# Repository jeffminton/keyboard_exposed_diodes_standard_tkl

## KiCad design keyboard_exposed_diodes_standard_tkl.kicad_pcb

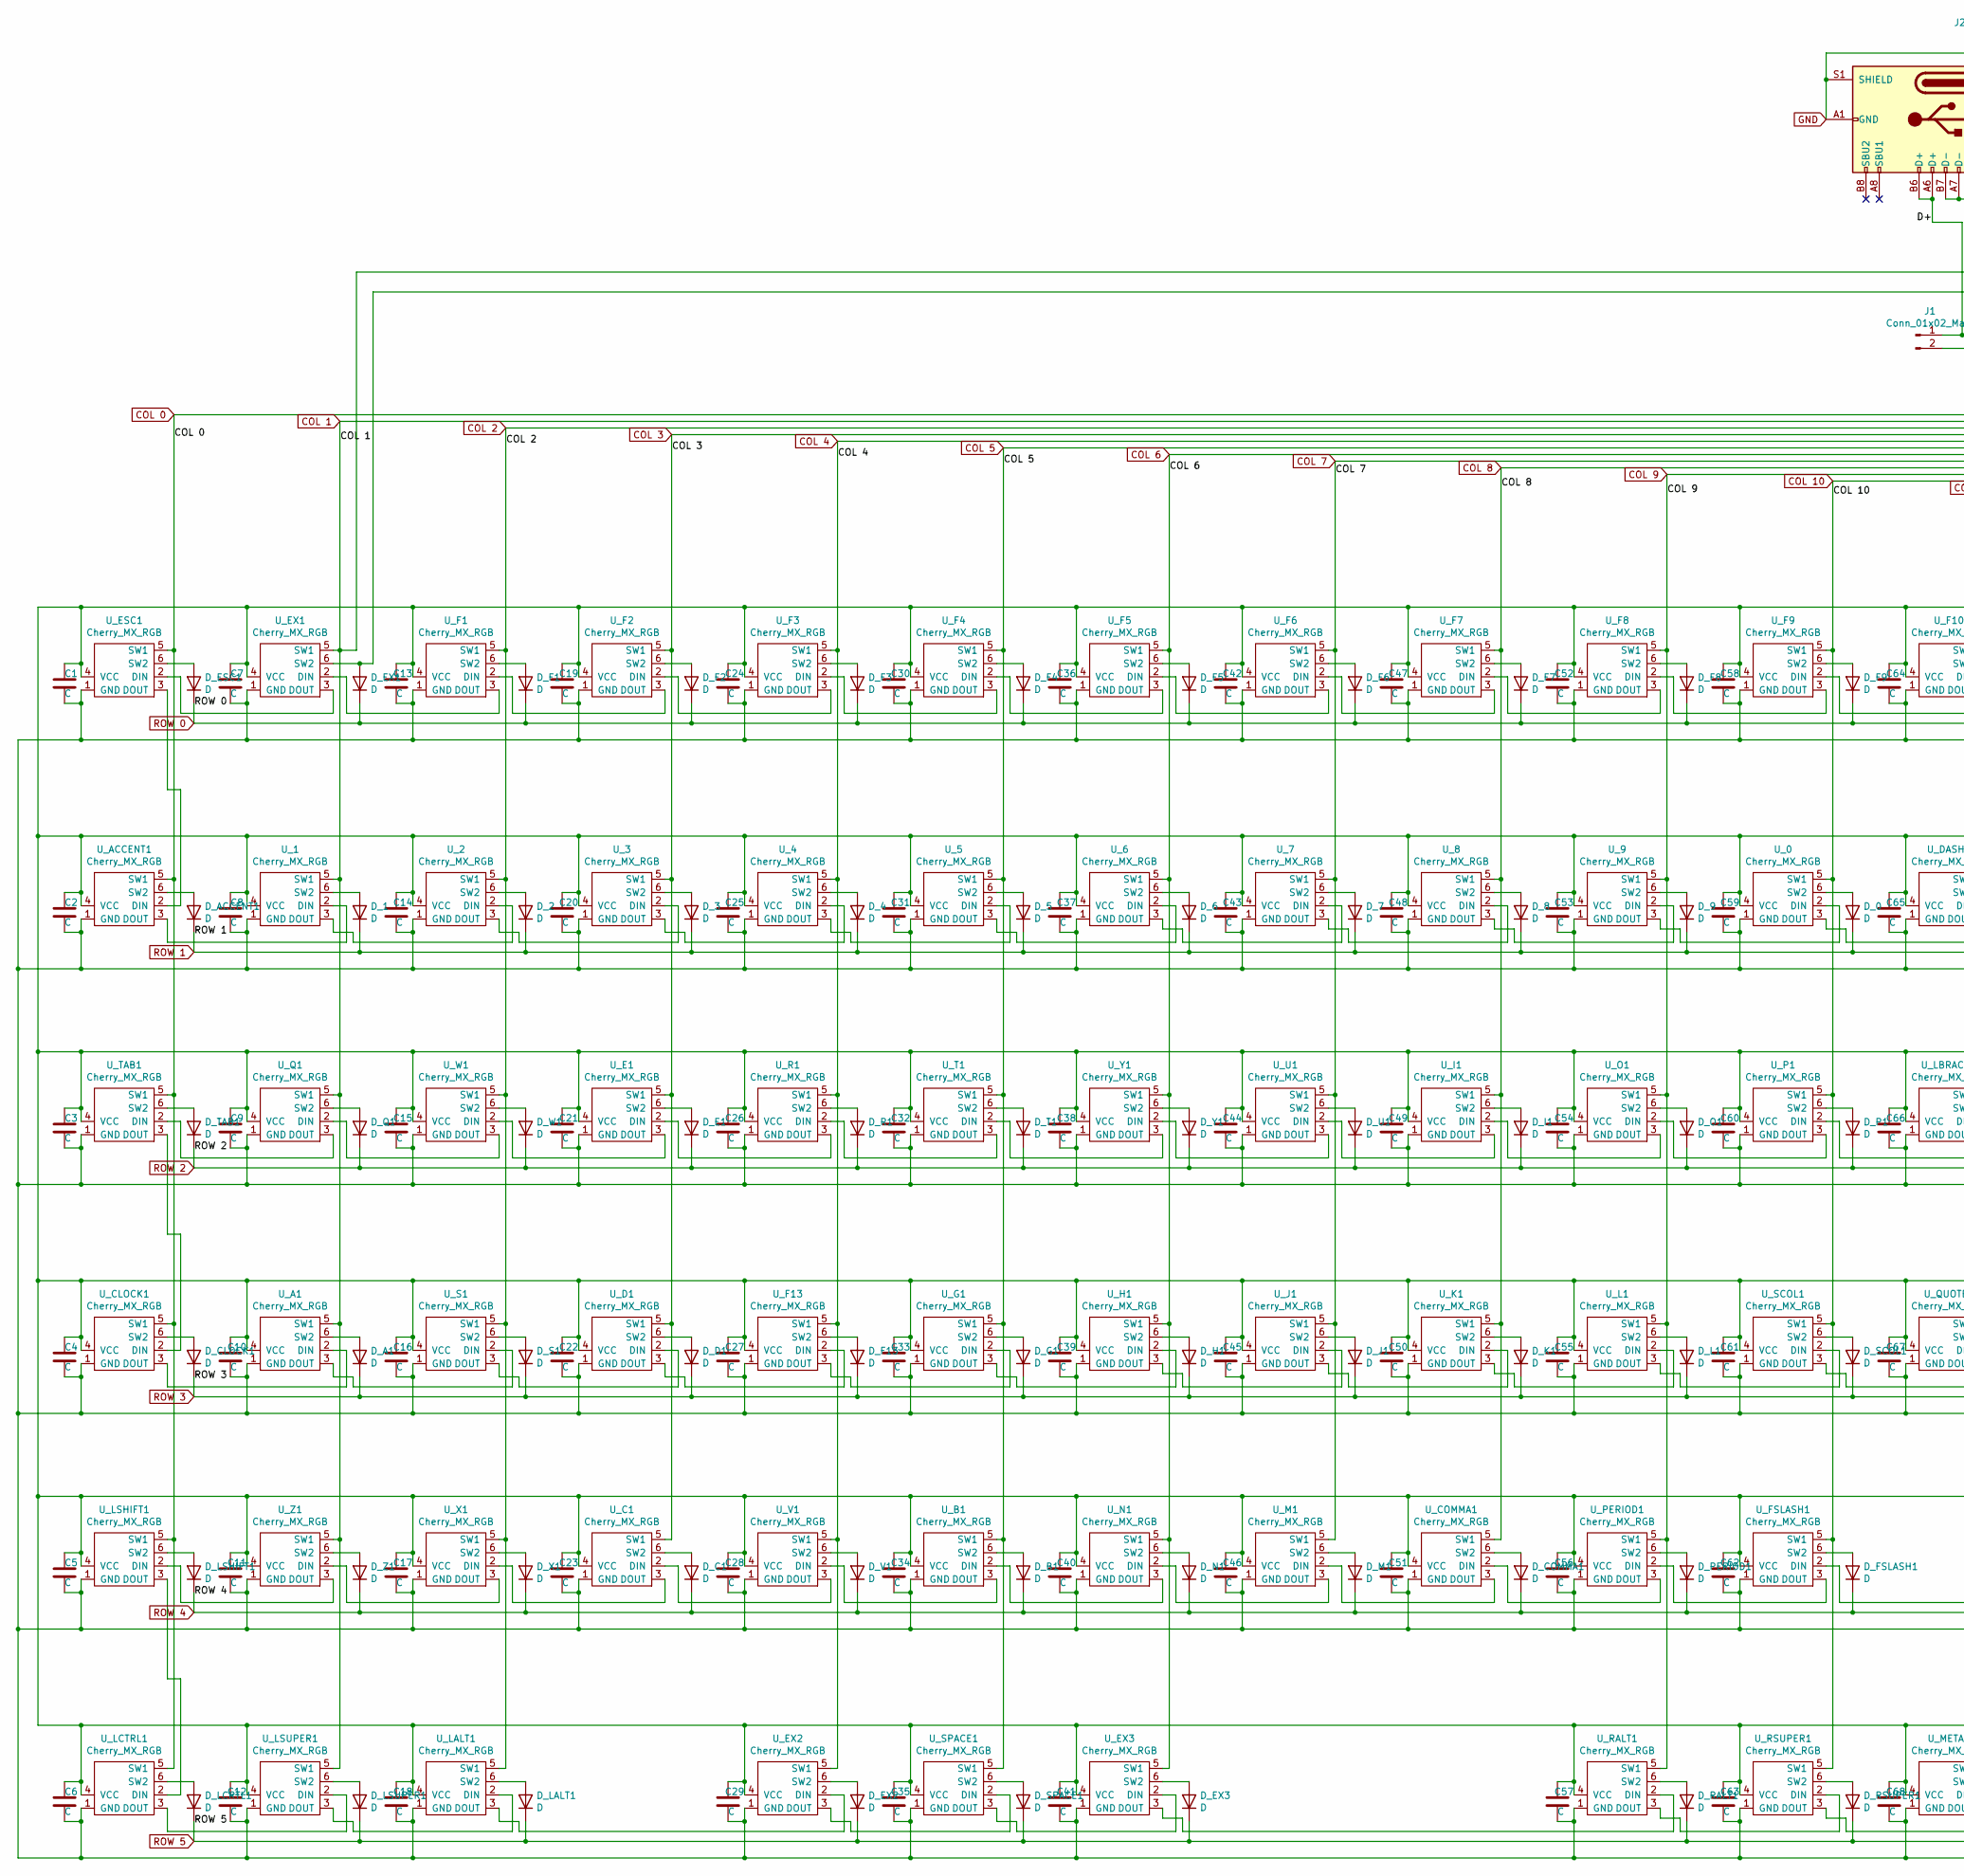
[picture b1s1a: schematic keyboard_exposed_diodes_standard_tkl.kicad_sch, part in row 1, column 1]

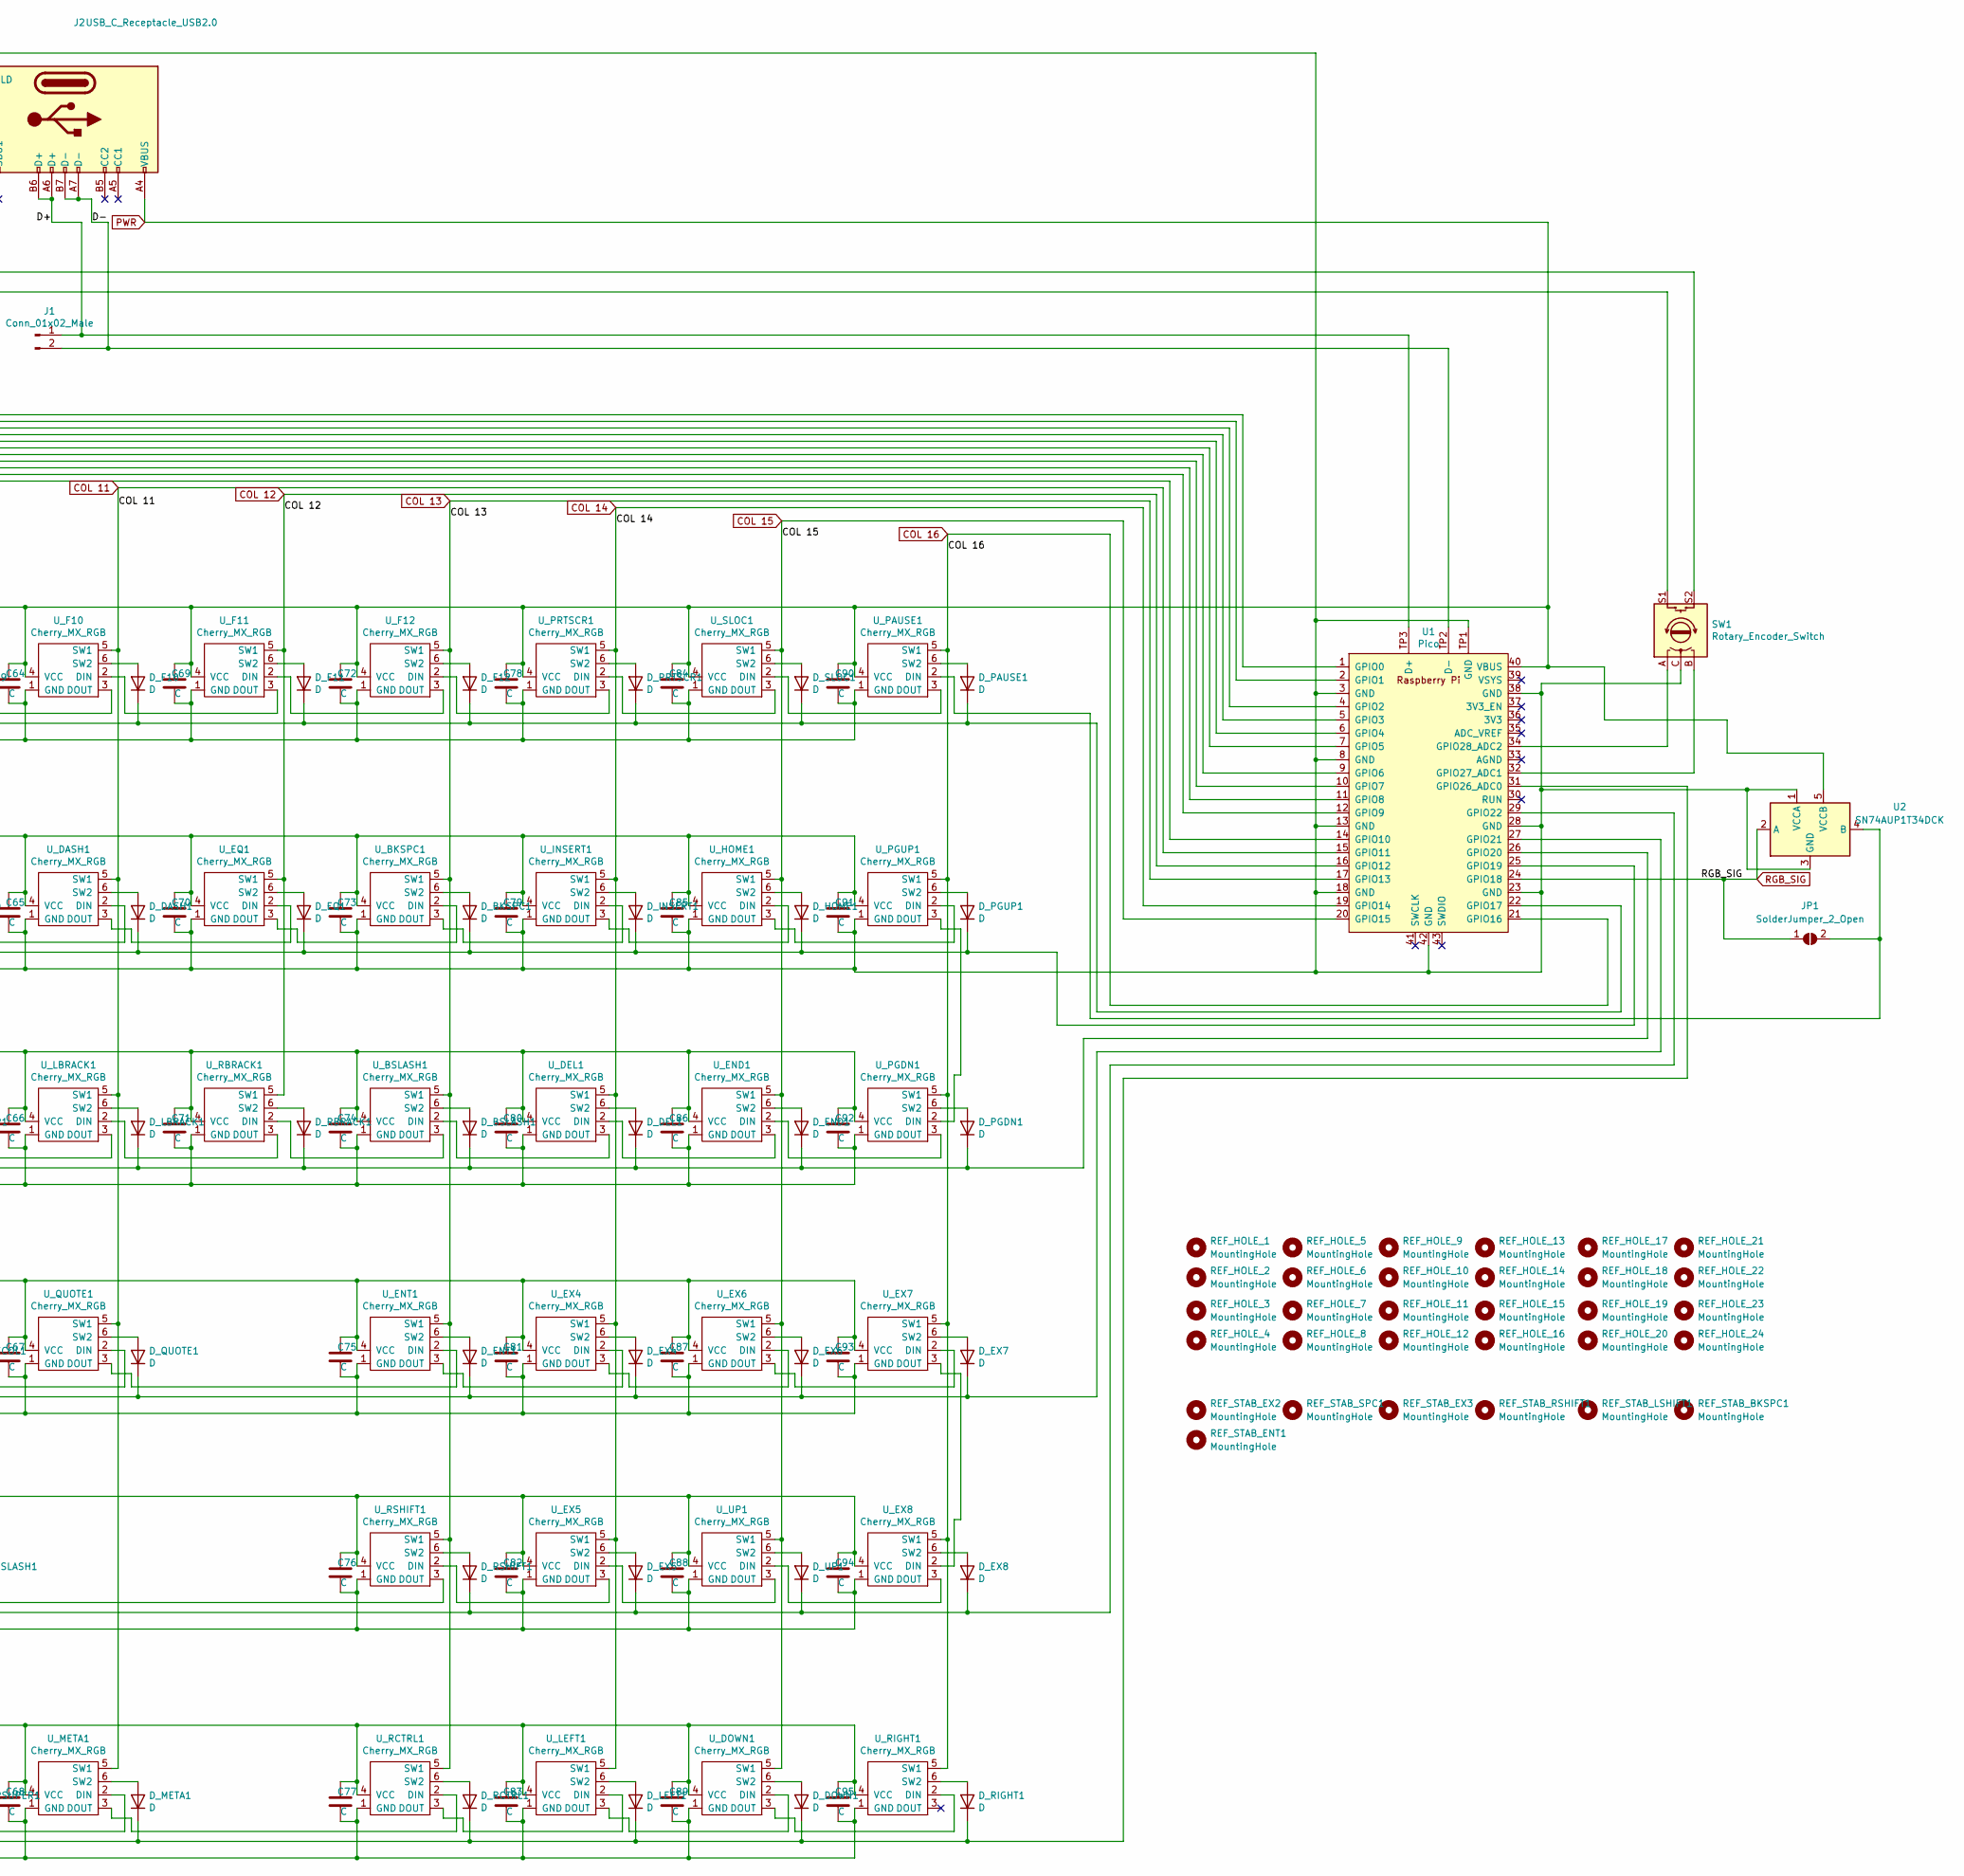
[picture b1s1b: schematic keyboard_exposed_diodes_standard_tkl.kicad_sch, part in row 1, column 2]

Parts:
C1, C2, C3, C4, C5, C6, C7, C8, C9, C10, C11, C12, C13, C14, C15, C16, C17, C18, C19, C20, C21, C22, C23, C24, C25, C26, C27, C28, C29, C30, C31, C32, C33, C34, C35, C36, C37, C38, C39, C40, C41, C42, C43, C44, C45, C46, C47, C48, C49, C50, C51, C52, C53, C54, C55, C56, C57, C58, C59, C60, C61, C62, C63, C64, C65, C66, C67, C68, C69, C70, C71, C72, C73, C74, C75, C76, C77, C78, C79, C80, C81, C82, C83, C84, C85, C86, C87, C88, C89, C90, C91, C92, C93, C94, C95: C; C_0805_2012Metric
D_0, D_1, D_2, D_3, D_4, D_5, D_6, D_7, D_8, D_9: D; D_DO-35_SOD27_P7.62mm_Horizontal
D_A1: D; D_DO-35_SOD27_P7.62mm_Horizontal
D_ACCENT1: D; D_DO-35_SOD27_P7.62mm_Horizontal
D_B1: D; D_DO-35_SOD27_P7.62mm_Horizontal
D_BKSPC1: D; D_DO-35_SOD27_P7.62mm_Horizontal
D_BSLASH1: D; D_DO-35_SOD27_P7.62mm_Horizontal
D_C1: D; D_DO-35_SOD27_P7.62mm_Horizontal
D_CLOCK1: D; D_DO-35_SOD27_P7.62mm_Horizontal
D_COMMA1: D; D_DO-35_SOD27_P7.62mm_Horizontal
D_D1: D; D_DO-35_SOD27_P7.62mm_Horizontal
D_DASH1: D; D_DO-35_SOD27_P7.62mm_Horizontal
D_DEL1: D; D_DO-35_SOD27_P7.62mm_Horizontal
D_DOWN1: D; D_DO-35_SOD27_P7.62mm_Horizontal
D_E1: D; D_DO-35_SOD27_P7.62mm_Horizontal
D_END1: D; D_DO-35_SOD27_P7.62mm_Horizontal
D_ENT1: D; D_DO-35_SOD27_P7.62mm_Horizontal
D_EQ1: D; D_DO-35_SOD27_P7.62mm_Horizontal
D_ESC1: D; D_DO-35_SOD27_P7.62mm_Horizontal
D_EX1, D_EX2, D_EX3, D_EX4, D_EX5, D_EX6, D_EX7, D_EX8: D; D_DO-35_SOD27_P7.62mm_Horizontal
D_F1, D_F2, D_F3, D_F4, D_F5, D_F6, D_F7, D_F8, D_F9, D_F10, D_F11, D_F12, D_F13: D; D_DO-35_SOD27_P7.62mm_Horizontal
D_FSLASH1: D; D_DO-35_SOD27_P7.62mm_Horizontal
D_G1: D; D_DO-35_SOD27_P7.62mm_Horizontal
D_H1: D; D_DO-35_SOD27_P7.62mm_Horizontal
D_HOME1: D; D_DO-35_SOD27_P7.62mm_Horizontal
D_I1: D; D_DO-35_SOD27_P7.62mm_Horizontal
D_INSERT1: D; D_DO-35_SOD27_P7.62mm_Horizontal
D_J1: D; D_DO-35_SOD27_P7.62mm_Horizontal
D_K1: D; D_DO-35_SOD27_P7.62mm_Horizontal
D_L1: D; D_DO-35_SOD27_P7.62mm_Horizontal
D_LALT1: D; D_DO-35_SOD27_P7.62mm_Horizontal
D_LBRACK1: D; D_DO-35_SOD27_P7.62mm_Horizontal
D_LCRTL1: D; D_DO-35_SOD27_P7.62mm_Horizontal
D_LEFT1: D; D_DO-35_SOD27_P7.62mm_Horizontal
D_LSHIFT1: D; D_DO-35_SOD27_P7.62mm_Horizontal
D_LSUPER1: D; D_DO-35_SOD27_P7.62mm_Horizontal
D_M1: D; D_DO-35_SOD27_P7.62mm_Horizontal
D_META1: D; D_DO-35_SOD27_P7.62mm_Horizontal
D_N1: D; D_DO-35_SOD27_P7.62mm_Horizontal
D_O1: D; D_DO-35_SOD27_P7.62mm_Horizontal
D_P1: D; D_DO-35_SOD27_P7.62mm_Horizontal
D_PAUSE1: D; D_DO-35_SOD27_P7.62mm_Horizontal
D_PERIOD1: D; D_DO-35_SOD27_P7.62mm_Horizontal
D_PGDN1: D; D_DO-35_SOD27_P7.62mm_Horizontal
D_PGUP1: D; D_DO-35_SOD27_P7.62mm_Horizontal
D_PRTSCR1: D; D_DO-35_SOD27_P7.62mm_Horizontal
D_Q1: D; D_DO-35_SOD27_P7.62mm_Horizontal
D_QUOTE1: D; D_DO-35_SOD27_P7.62mm_Horizontal
D_R1: D; D_DO-35_SOD27_P7.62mm_Horizontal
D_RALT1: D; D_DO-35_SOD27_P7.62mm_Horizontal
D_RBRACK1: D; D_DO-35_SOD27_P7.62mm_Horizontal
D_RCTRL1: D; D_DO-35_SOD27_P7.62mm_Horizontal
D_RIGHT1: D; D_DO-35_SOD27_P7.62mm_Horizontal
D_RSHIFT1: D; D_DO-35_SOD27_P7.62mm_Horizontal
D_RSUPER1: D; D_DO-35_SOD27_P7.62mm_Horizontal
D_S1: D; D_DO-35_SOD27_P7.62mm_Horizontal
D_SCOL1: D; D_DO-35_SOD27_P7.62mm_Horizontal
D_SLOC1: D; D_DO-35_SOD27_P7.62mm_Horizontal
D_SPACE1: D; D_DO-35_SOD27_P7.62mm_Horizontal
D_T1: D; D_DO-35_SOD27_P7.62mm_Horizontal
D_TAB1: D; D_DO-35_SOD27_P7.62mm_Horizontal
D_U1: D; D_DO-35_SOD27_P7.62mm_Horizontal
D_UP1: D; D_DO-35_SOD27_P7.62mm_Horizontal
D_V1: D; D_DO-35_SOD27_P7.62mm_Horizontal
D_W1: D; D_DO-35_SOD27_P7.62mm_Horizontal
D_X1: D; D_DO-35_SOD27_P7.62mm_Horizontal
D_Y1: D; D_DO-35_SOD27_P7.62mm_Horizontal
D_Z1: D; D_DO-35_SOD27_P7.62mm_Horizontal
J1: Conn_01x02_Male; PinHeader_1x02_P2.54mm_Vertical
J2: USB_C_Receptacle_USB2.0; USB_C_Receptacle_GCT_USB4085
JP1: SolderJumper_2_Open; SolderJumper-2_P1.3mm_Open_RoundedPad1.0x1.5mm
REF_HOLE_1, REF_HOLE_2, REF_HOLE_3, REF_HOLE_4, REF_HOLE_5, REF_HOLE_6, REF_HOLE_7, REF_HOLE_8, REF_HOLE_9, REF_HOLE_10, REF_HOLE_11, REF_HOLE_12, REF_HOLE_13, REF_HOLE_14, REF_HOLE_15, REF_HOLE_16, REF_HOLE_17, REF_HOLE_18, REF_HOLE_19, REF_HOLE_20, REF_HOLE_21, REF_HOLE_22, REF_HOLE_23, REF_HOLE_24: MountingHole; MountingHole_4.3mm_M4
REF_STAB_BKSPC1: MountingHole; Stabilizer_Cherry_MX_2u
REF_STAB_ENT1: MountingHole; Stabilizer_Cherry_MX_2u
REF_STAB_EX2, REF_STAB_EX3: MountingHole; Stabilizer_Cherry_MX_2u
REF_STAB_LSHIFT1: MountingHole; Stabilizer_Cherry_MX_2u
REF_STAB_RSHIFT1: MountingHole; Stabilizer_Cherry_MX_2u
REF_STAB_SPC1: MountingHole; Stabilizer_Cherry_MX_2u
SW1: Rotary_Encoder_Switch; Rotary_Encoder_Switched_PEC11R
U1: Pico; RPi_Pico_SMD_TH
U2: SN74AUP1T34DCK; SOT-353_SC-70-5
U_0, U_1, U_2, U_3, U_4, U_5, U_6, U_7, U_8, U_9: Cherry_MX_RGB; Cherry-MX_PCB-Mounted_LTST-A683CEGBW_Mill-Max-7305
U_A1: Cherry_MX_RGB; Cherry-MX_PCB-Mounted_LTST-A683CEGBW_Mill-Max-7305
U_ACCENT1: Cherry_MX_RGB; Cherry-MX_PCB-Mounted_LTST-A683CEGBW_Mill-Max-7305
U_B1: Cherry_MX_RGB; Cherry-MX_PCB-Mounted_LTST-A683CEGBW_Mill-Max-7305
U_BKSPC1: Cherry_MX_RGB; Cherry-MX_PCB-Mounted_LTST-A683CEGBW_Mill-Max-7305
U_BSLASH1: Cherry_MX_RGB; Cherry-MX_PCB-Mounted_LTST-A683CEGBW_Mill-Max-7305
U_C1: Cherry_MX_RGB; Cherry-MX_PCB-Mounted_LTST-A683CEGBW_Mill-Max-7305
U_CLOCK1: Cherry_MX_RGB; Cherry-MX_PCB-Mounted_LTST-A683CEGBW_Mill-Max-7305
U_COMMA1: Cherry_MX_RGB; Cherry-MX_PCB-Mounted_LTST-A683CEGBW_Mill-Max-7305
U_D1: Cherry_MX_RGB; Cherry-MX_PCB-Mounted_LTST-A683CEGBW_Mill-Max-7305
U_DASH1: Cherry_MX_RGB; Cherry-MX_PCB-Mounted_LTST-A683CEGBW_Mill-Max-7305
U_DEL1: Cherry_MX_RGB; Cherry-MX_PCB-Mounted_LTST-A683CEGBW_Mill-Max-7305
U_DOWN1: Cherry_MX_RGB; Cherry-MX_PCB-Mounted_LTST-A683CEGBW_Mill-Max-7305
U_E1: Cherry_MX_RGB; Cherry-MX_PCB-Mounted_LTST-A683CEGBW_Mill-Max-7305
U_END1: Cherry_MX_RGB; Cherry-MX_PCB-Mounted_LTST-A683CEGBW_Mill-Max-7305
U_ENT1: Cherry_MX_RGB; Cherry-MX_PCB-Mounted_LTST-A683CEGBW_Mill-Max-7305
U_EQ1: Cherry_MX_RGB; Cherry-MX_PCB-Mounted_LTST-A683CEGBW_Mill-Max-7305
U_ESC1: Cherry_MX_RGB; Cherry-MX_PCB-Mounted_LTST-A683CEGBW_Mill-Max-7305
U_EX1, U_EX2, U_EX3, U_EX4, U_EX5, U_EX6, U_EX7, U_EX8: Cherry_MX_RGB; Cherry-MX_PCB-Mounted_LTST-A683CEGBW_Mill-Max-7305
U_F1, U_F2, U_F3, U_F4, U_F5, U_F6, U_F7, U_F8, U_F9, U_F10, U_F11, U_F12, U_F13: Cherry_MX_RGB; Cherry-MX_PCB-Mounted_LTST-A683CEGBW_Mill-Max-7305
U_FSLASH1: Cherry_MX_RGB; Cherry-MX_PCB-Mounted_LTST-A683CEGBW_Mill-Max-7305
U_G1: Cherry_MX_RGB; Cherry-MX_PCB-Mounted_LTST-A683CEGBW_Mill-Max-7305
U_H1: Cherry_MX_RGB; Cherry-MX_PCB-Mounted_LTST-A683CEGBW_Mill-Max-7305
U_HOME1: Cherry_MX_RGB; Cherry-MX_PCB-Mounted_LTST-A683CEGBW_Mill-Max-7305
U_I1: Cherry_MX_RGB; Cherry-MX_PCB-Mounted_LTST-A683CEGBW_Mill-Max-7305
U_INSERT1: Cherry_MX_RGB; Cherry-MX_PCB-Mounted_LTST-A683CEGBW_Mill-Max-7305
U_J1: Cherry_MX_RGB; Cherry-MX_PCB-Mounted_LTST-A683CEGBW_Mill-Max-7305
U_K1: Cherry_MX_RGB; Cherry-MX_PCB-Mounted_LTST-A683CEGBW_Mill-Max-7305
U_L1: Cherry_MX_RGB; Cherry-MX_PCB-Mounted_LTST-A683CEGBW_Mill-Max-7305
U_LALT1: Cherry_MX_RGB; Cherry-MX_PCB-Mounted_LTST-A683CEGBW_Mill-Max-7305
U_LBRACK1: Cherry_MX_RGB; Cherry-MX_PCB-Mounted_LTST-A683CEGBW_Mill-Max-7305
U_LCTRL1: Cherry_MX_RGB; Cherry-MX_PCB-Mounted_LTST-A683CEGBW_Mill-Max-7305
U_LEFT1: Cherry_MX_RGB; Cherry-MX_PCB-Mounted_LTST-A683CEGBW_Mill-Max-7305
U_LSHIFT1: Cherry_MX_RGB; Cherry-MX_PCB-Mounted_LTST-A683CEGBW_Mill-Max-7305
U_LSUPER1: Cherry_MX_RGB; Cherry-MX_PCB-Mounted_LTST-A683CEGBW_Mill-Max-7305
U_M1: Cherry_MX_RGB; Cherry-MX_PCB-Mounted_LTST-A683CEGBW_Mill-Max-7305
U_META1: Cherry_MX_RGB; Cherry-MX_PCB-Mounted_LTST-A683CEGBW_Mill-Max-7305
U_N1: Cherry_MX_RGB; Cherry-MX_PCB-Mounted_LTST-A683CEGBW_Mill-Max-7305
U_O1: Cherry_MX_RGB; Cherry-MX_PCB-Mounted_LTST-A683CEGBW_Mill-Max-7305
U_P1: Cherry_MX_RGB; Cherry-MX_PCB-Mounted_LTST-A683CEGBW_Mill-Max-7305
U_PAUSE1: Cherry_MX_RGB; Cherry-MX_PCB-Mounted_LTST-A683CEGBW_Mill-Max-7305
U_PERIOD1: Cherry_MX_RGB; Cherry-MX_PCB-Mounted_LTST-A683CEGBW_Mill-Max-7305
U_PGDN1: Cherry_MX_RGB; Cherry-MX_PCB-Mounted_LTST-A683CEGBW_Mill-Max-7305
U_PGUP1: Cherry_MX_RGB; Cherry-MX_PCB-Mounted_LTST-A683CEGBW_Mill-Max-7305
U_PRTSCR1: Cherry_MX_RGB; Cherry-MX_PCB-Mounted_LTST-A683CEGBW_Mill-Max-7305
U_Q1: Cherry_MX_RGB; Cherry-MX_PCB-Mounted_LTST-A683CEGBW_Mill-Max-7305
U_QUOTE1: Cherry_MX_RGB; Cherry-MX_PCB-Mounted_LTST-A683CEGBW_Mill-Max-7305
U_R1: Cherry_MX_RGB; Cherry-MX_PCB-Mounted_LTST-A683CEGBW_Mill-Max-7305
U_RALT1: Cherry_MX_RGB; Cherry-MX_PCB-Mounted_LTST-A683CEGBW_Mill-Max-7305
U_RBRACK1: Cherry_MX_RGB; Cherry-MX_PCB-Mounted_LTST-A683CEGBW_Mill-Max-7305
U_RCTRL1: Cherry_MX_RGB; Cherry-MX_PCB-Mounted_LTST-A683CEGBW_Mill-Max-7305
U_RIGHT1: Cherry_MX_RGB; Cherry-MX_PCB-Mounted_LTST-A683CEGBW_Mill-Max-7305
U_RSHIFT1: Cherry_MX_RGB; Cherry-MX_PCB-Mounted_LTST-A683CEGBW_Mill-Max-7305
U_RSUPER1: Cherry_MX_RGB; Cherry-MX_PCB-Mounted_LTST-A683CEGBW_Mill-Max-7305
U_S1: Cherry_MX_RGB; Cherry-MX_PCB-Mounted_LTST-A683CEGBW_Mill-Max-7305
U_SCOL1: Cherry_MX_RGB; Cherry-MX_PCB-Mounted_LTST-A683CEGBW_Mill-Max-7305
U_SLOC1: Cherry_MX_RGB; Cherry-MX_PCB-Mounted_LTST-A683CEGBW_Mill-Max-7305
U_SPACE1: Cherry_MX_RGB; Cherry-MX_PCB-Mounted_LTST-A683CEGBW_Mill-Max-7305
U_T1: Cherry_MX_RGB; Cherry-MX_PCB-Mounted_LTST-A683CEGBW_Mill-Max-7305
U_TAB1: Cherry_MX_RGB; Cherry-MX_PCB-Mounted_LTST-A683CEGBW_Mill-Max-7305
U_U1: Cherry_MX_RGB; Cherry-MX_PCB-Mounted_LTST-A683CEGBW_Mill-Max-7305
U_UP1: Cherry_MX_RGB; Cherry-MX_PCB-Mounted_LTST-A683CEGBW_Mill-Max-7305
U_V1: Cherry_MX_RGB; Cherry-MX_PCB-Mounted_LTST-A683CEGBW_Mill-Max-7305
U_W1: Cherry_MX_RGB; Cherry-MX_PCB-Mounted_LTST-A683CEGBW_Mill-Max-7305
U_X1: Cherry_MX_RGB; Cherry-MX_PCB-Mounted_LTST-A683CEGBW_Mill-Max-7305
U_Y1: Cherry_MX_RGB; Cherry-MX_PCB-Mounted_LTST-A683CEGBW_Mill-Max-7305
U_Z1: Cherry_MX_RGB; Cherry-MX_PCB-Mounted_LTST-A683CEGBW_Mill-Max-7305

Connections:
/D+: J1.1, J2.A6 (D+), J2.B6 (D+), U1.TP3 (D+)
/D-: J1.2, J2.A7 (D-), J2.B7 (D-), U1.TP2 (D-)
COL 0: U1.1 (GPIO0), U_ACCENT1.5 (SW1), U_CLOCK1.5 (SW1), U_ESC1.5 (SW1), U_LCTRL1.5 (SW1), U_LSHIFT1.5 (SW1), U_TAB1.5 (SW1)
COL 1: SW1.S2, U1.2 (GPIO1), U_1.5 (SW1), U_A1.5 (SW1), U_EX1.5 (SW1), U_LSUPER1.5 (SW1), U_Q1.5 (SW1), U_Z1.5 (SW1)
COL 2: U1.4 (GPIO2), U_2.5 (SW1), U_F1.5 (SW1), U_LALT1.5 (SW1), U_S1.5 (SW1), U_W1.5 (SW1), U_X1.5 (SW1)
COL 3: U1.5 (GPIO3), U_3.5 (SW1), U_C1.5 (SW1), U_D1.5 (SW1), U_E1.5 (SW1), U_F2.5 (SW1)
COL 4: U1.6 (GPIO4), U_4.5 (SW1), U_EX2.5 (SW1), U_F3.5 (SW1), U_F13.5 (SW1), U_R1.5 (SW1), U_V1.5 (SW1)
COL 5: U1.7 (GPIO5), U_5.5 (SW1), U_B1.5 (SW1), U_F4.5 (SW1), U_G1.5 (SW1), U_SPACE1.5 (SW1), U_T1.5 (SW1)
COL 6: U1.9 (GPIO6), U_6.5 (SW1), U_EX3.5 (SW1), U_F5.5 (SW1), U_H1.5 (SW1), U_N1.5 (SW1), U_Y1.5 (SW1)
COL 7: U1.10 (GPIO7), U_7.5 (SW1), U_F6.5 (SW1), U_J1.5 (SW1), U_M1.5 (SW1), U_U1.5 (SW1)
COL 8: U1.11 (GPIO8), U_8.5 (SW1), U_COMMA1.5 (SW1), U_F7.5 (SW1), U_I1.5 (SW1), U_K1.5 (SW1)
COL 9: U1.12 (GPIO9), U_9.5 (SW1), U_F8.5 (SW1), U_L1.5 (SW1), U_O1.5 (SW1), U_PERIOD1.5 (SW1), U_RALT1.5 (SW1)
COL 10: U1.14 (GPIO10), U_0.5 (SW1), U_F9.5 (SW1), U_FSLASH1.5 (SW1), U_P1.5 (SW1), U_RSUPER1.5 (SW1), U_SCOL1.5 (SW1)
COL 11: U1.15 (GPIO11), U_DASH1.5 (SW1), U_F10.5 (SW1), U_LBRACK1.5 (SW1), U_META1.5 (SW1), U_QUOTE1.5 (SW1)
COL 12: U1.16 (GPIO12), U_EQ1.5 (SW1), U_F11.5 (SW1), U_RBRACK1.5 (SW1)
COL 13: U1.17 (GPIO13), U_BKSPC1.5 (SW1), U_BSLASH1.5 (SW1), U_ENT1.5 (SW1), U_F12.5 (SW1), U_RCTRL1.5 (SW1), U_RSHIFT1.5 (SW1)
COL 14: U1.19 (GPIO14), U_DEL1.5 (SW1), U_EX4.5 (SW1), U_EX5.5 (SW1), U_INSERT1.5 (SW1), U_LEFT1.5 (SW1), U_PRTSCR1.5 (SW1)
COL 15: U1.20 (GPIO15), U_DOWN1.5 (SW1), U_END1.5 (SW1), U_EX6.5 (SW1), U_HOME1.5 (SW1), U_SLOC1.5 (SW1), U_UP1.5 (SW1)
COL 16: U1.21 (GPIO16), U_EX7.5 (SW1), U_EX8.5 (SW1), U_PAUSE1.5 (SW1), U_PGDN1.5 (SW1), U_PGUP1.5 (SW1), U_RIGHT1.5 (SW1)
GND: C1.2, C2.2, C3.2, C4.2, C5.2, C6.2, C7.2, C8.2, C9.2, C10.2, C11.2, C12.2, C13.2, C14.2, C15.2, C16.2, C17.2, C18.2, C19.2, C20.2, C21.2, C22.2, C23.2, C24.2, C25.2, C26.2, C27.2, C28.2, C29.2, C30.2, C31.2, C32.2, C33.2, C34.2, C35.2, C36.2, C37.2, C38.2, C39.2, C40.2, C41.2, C42.2, C43.2, C44.2, C45.2, C46.2, C47.2, C48.2, C49.2, C50.2, C51.2, C52.2, C53.2, C54.2, C55.2, C56.2, C57.2, C58.2, C59.2, C60.2, C61.2, C62.2, C63.2, C64.2, C65.2, C66.2, C67.2, C68.2, C69.2, C70.2, C71.2, C72.2, C73.2, C74.2, C75.2, C76.2, C77.2, C78.2, C79.2, C80.2, C81.2, C82.2, C83.2, C84.2, C85.2, C86.2, C87.2, C88.2, C89.2, C90.2, C91.2, C92.2, C93.2, C94.2, C95.2, J2.A1 (GND), J2.A12 (GND), J2.B1 (GND), J2.B12 (GND), J2.S1 (SHIELD), SW1.C, U1.3 (GND), U1.8 (GND), U1.13 (GND), U1.18 (GND), U1.23 (GND), U1.28 (GND), U1.38 (GND), U1.42 (GND), U1.TP1 (GND), U2.1 (VCCA), U2.3 (GND), U_0.1 (GND), U_1.1 (GND), U_2.1 (GND), U_3.1 (GND), U_4.1 (GND), U_5.1 (GND), U_6.1 (GND), U_7.1 (GND), U_8.1 (GND)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
unnamed: D_0.2 (A), U_0.6 (SW2)
unnamed: D_1.2 (A), U_1.6 (SW2)
unnamed: D_2.2 (A), U_2.6 (SW2)
unnamed: D_3.2 (A), U_3.6 (SW2)
unnamed: D_4.2 (A), U_4.6 (SW2)
unnamed: D_5.2 (A), U_5.6 (SW2)
unnamed: D_6.2 (A), U_6.6 (SW2)
unnamed: D_7.2 (A), U_7.6 (SW2)
unnamed: D_8.2 (A), U_8.6 (SW2)
unnamed: D_9.2 (A), U_9.6 (SW2)
unnamed: D_A1.2 (A), U_A1.6 (SW2)
unnamed: D_ACCENT1.2 (A), U_ACCENT1.6 (SW2)
unnamed: D_B1.2 (A), U_B1.6 (SW2)
unnamed: D_BKSPC1.2 (A), U_BKSPC1.6 (SW2)
unnamed: D_BSLASH1.2 (A), U_BSLASH1.6 (SW2)
unnamed: D_C1.2 (A), U_C1.6 (SW2)
unnamed: D_CLOCK1.2 (A), U_CLOCK1.6 (SW2)
unnamed: D_COMMA1.2 (A), U_COMMA1.6 (SW2)
unnamed: D_D1.2 (A), U_D1.6 (SW2)
unnamed: D_DASH1.2 (A), U_DASH1.6 (SW2)
unnamed: D_DEL1.2 (A), U_DEL1.6 (SW2)
unnamed: D_DOWN1.2 (A), U_DOWN1.6 (SW2)
unnamed: D_E1.2 (A), U_E1.6 (SW2)
unnamed: D_END1.2 (A), U_END1.6 (SW2)
unnamed: D_ENT1.2 (A), U_ENT1.6 (SW2)
unnamed: D_EQ1.2 (A), U_EQ1.6 (SW2)
unnamed: D_ESC1.2 (A), U_ESC1.6 (SW2)
unnamed: D_EX1.2 (A), SW1.S1, U_EX1.6 (SW2)
unnamed: D_EX2.2 (A), U_EX2.6 (SW2)
unnamed: D_EX3.2 (A), U_EX3.6 (SW2)
unnamed: D_EX4.2 (A), U_EX4.6 (SW2)
unnamed: D_EX5.2 (A), U_EX5.6 (SW2)
unnamed: D_EX6.2 (A), U_EX6.6 (SW2)
unnamed: D_EX7.2 (A), U_EX7.6 (SW2)
unnamed: D_EX8.2 (A), U_EX8.6 (SW2)
unnamed: D_F1.2 (A), U_F1.6 (SW2)
unnamed: D_F2.2 (A), U_F2.6 (SW2)
unnamed: D_F3.2 (A), U_F3.6 (SW2)
unnamed: D_F4.2 (A), U_F4.6 (SW2)
unnamed: D_F5.2 (A), U_F5.6 (SW2)
unnamed: D_F6.2 (A), U_F6.6 (SW2)
unnamed: D_F7.2 (A), U_F7.6 (SW2)
unnamed: D_F8.2 (A), U_F8.6 (SW2)
unnamed: D_F9.2 (A), U_F9.6 (SW2)
unnamed: D_F10.2 (A), U_F10.6 (SW2)
unnamed: D_F11.2 (A), U_F11.6 (SW2)
unnamed: D_F12.2 (A), U_F12.6 (SW2)
unnamed: D_F13.2 (A), U_F13.6 (SW2)
unnamed: D_FSLASH1.2 (A), U_FSLASH1.6 (SW2)
unnamed: D_G1.2 (A), U_G1.6 (SW2)
unnamed: D_H1.2 (A), U_H1.6 (SW2)
unnamed: D_HOME1.2 (A), U_HOME1.6 (SW2)
unnamed: D_I1.2 (A), U_I1.6 (SW2)
unnamed: D_INSERT1.2 (A), U_INSERT1.6 (SW2)
unnamed: D_J1.2 (A), U_J1.6 (SW2)
unnamed: D_K1.2 (A), U_K1.6 (SW2)
unnamed: D_L1.2 (A), U_L1.6 (SW2)
unnamed: D_LALT1.2 (A), U_LALT1.6 (SW2)
unnamed: D_LBRACK1.2 (A), U_LBRACK1.6 (SW2)
unnamed: D_LCRTL1.2 (A), U_LCTRL1.6 (SW2)
unnamed: D_LEFT1.2 (A), U_LEFT1.6 (SW2)
unnamed: D_LSHIFT1.2 (A), U_LSHIFT1.6 (SW2)
unnamed: D_LSUPER1.2 (A), U_LSUPER1.6 (SW2)
unnamed: D_M1.2 (A), U_M1.6 (SW2)
unnamed: D_META1.2 (A), U_META1.6 (SW2)
unnamed: D_N1.2 (A), U_N1.6 (SW2)
unnamed: D_O1.2 (A), U_O1.6 (SW2)
unnamed: D_P1.2 (A), U_P1.6 (SW2)
unnamed: D_PAUSE1.2 (A), U_PAUSE1.6 (SW2)
unnamed: D_PERIOD1.2 (A), U_PERIOD1.6 (SW2)
unnamed: D_PGDN1.2 (A), U_PGDN1.6 (SW2)
unnamed: D_PGUP1.2 (A), U_PGUP1.6 (SW2)
unnamed: D_PRTSCR1.2 (A), U_PRTSCR1.6 (SW2)
unnamed: D_Q1.2 (A), U_Q1.6 (SW2)
unnamed: D_QUOTE1.2 (A), U_QUOTE1.6 (SW2)
unnamed: D_R1.2 (A), U_R1.6 (SW2)
unnamed: D_RALT1.2 (A), U_RALT1.6 (SW2)
unnamed: D_RBRACK1.2 (A), U_RBRACK1.6 (SW2)
unnamed: D_RCTRL1.2 (A), U_RCTRL1.6 (SW2)
unnamed: D_RIGHT1.2 (A), U_RIGHT1.6 (SW2)
unnamed: D_RSHIFT1.2 (A), U_RSHIFT1.6 (SW2)
unnamed: D_RSUPER1.2 (A), U_RSUPER1.6 (SW2)
unnamed: D_S1.2 (A), U_S1.6 (SW2)
unnamed: D_SCOL1.2 (A), U_SCOL1.6 (SW2)
unnamed: D_SLOC1.2 (A), U_SLOC1.6 (SW2)
unnamed: D_SPACE1.2 (A), U_SPACE1.6 (SW2)
unnamed: D_T1.2 (A), U_T1.6 (SW2)
unnamed: D_TAB1.2 (A), U_TAB1.6 (SW2)
unnamed: D_U1.2 (A), U_U1.6 (SW2)
unnamed: D_UP1.2 (A), U_UP1.6 (SW2)
unnamed: D_V1.2 (A), U_V1.6 (SW2)
unnamed: D_W1.2 (A), U_W1.6 (SW2)
unnamed: D_X1.2 (A), U_X1.6 (SW2)
unnamed: D_Y1.2 (A), U_Y1.6 (SW2)
unnamed: D_Z1.2 (A), U_Z1.6 (SW2)
unnamed: JP1.2 (B), U2.4 (B), U_PAUSE1.2 (DIN)
unnamed: SW1.A, U1.34 (GPIO28_ADC2)
unnamed: SW1.B, U1.32 (GPIO27_ADC1)
unnamed: U_0.2 (DIN), U_9.3 (DOUT)
unnamed: U_0.3 (DOUT), U_DASH1.2 (DIN)
unnamed: U_1.2 (DIN), U_ACCENT1.3 (DOUT)
unnamed: U_1.3 (DOUT), U_2.2 (DIN)
unnamed: U_2.3 (DOUT), U_3.2 (DIN)
unnamed: U_3.3 (DOUT), U_4.2 (DIN)
unnamed: U_4.3 (DOUT), U_5.2 (DIN)
unnamed: U_5.3 (DOUT), U_6.2 (DIN)
unnamed: U_6.3 (DOUT), U_7.2 (DIN)
unnamed: U_7.3 (DOUT), U_8.2 (DIN)
unnamed: U_8.3 (DOUT), U_9.2 (DIN)
unnamed: U_A1.2 (DIN), U_CLOCK1.3 (DOUT)
unnamed: U_A1.3 (DOUT), U_S1.2 (DIN)
unnamed: U_ACCENT1.2 (DIN), U_ESC1.3 (DOUT)
unnamed: U_B1.2 (DIN), U_N1.3 (DOUT)
unnamed: U_B1.3 (DOUT), U_V1.2 (DIN)
unnamed: U_BKSPC1.2 (DIN), U_EQ1.3 (DOUT)
unnamed: U_BKSPC1.3 (DOUT), U_INSERT1.2 (DIN)
unnamed: U_BSLASH1.2 (DIN), U_DEL1.3 (DOUT)
unnamed: U_BSLASH1.3 (DOUT), U_RBRACK1.2 (DIN)
unnamed: U_C1.2 (DIN), U_V1.3 (DOUT)
unnamed: U_C1.3 (DOUT), U_X1.2 (DIN)
unnamed: U_CLOCK1.2 (DIN), U_TAB1.3 (DOUT)
unnamed: U_COMMA1.2 (DIN), U_PERIOD1.3 (DOUT)
unnamed: U_COMMA1.3 (DOUT), U_M1.2 (DIN)
unnamed: U_D1.2 (DIN), U_S1.3 (DOUT)
unnamed: U_D1.3 (DOUT), U_F13.2 (DIN)
unnamed: U_DASH1.3 (DOUT), U_EQ1.2 (DIN)
unnamed: U_DEL1.2 (DIN), U_END1.3 (DOUT)
unnamed: U_DOWN1.2 (DIN), U_LEFT1.3 (DOUT)
unnamed: U_DOWN1.3 (DOUT), U_RIGHT1.2 (DIN)
unnamed: U_E1.2 (DIN), U_R1.3 (DOUT)
unnamed: U_E1.3 (DOUT), U_W1.2 (DIN)
unnamed: U_END1.2 (DIN), U_PGDN1.3 (DOUT)
unnamed: U_ENT1.2 (DIN), U_QUOTE1.3 (DOUT)
unnamed: U_ENT1.3 (DOUT), U_EX4.2 (DIN)
unnamed: U_ESC1.2 (DIN), U_EX1.3 (DOUT)
unnamed: U_EX1.2 (DIN), U_F1.3 (DOUT)
unnamed: U_EX2.2 (DIN), U_LALT1.3 (DOUT)
unnamed: U_EX2.3 (DOUT), U_SPACE1.2 (DIN)
unnamed: U_EX3.2 (DIN), U_SPACE1.3 (DOUT)
unnamed: U_EX3.3 (DOUT), U_RALT1.2 (DIN)
unnamed: U_EX4.3 (DOUT), U_EX6.2 (DIN)
unnamed: U_EX5.2 (DIN), U_UP1.3 (DOUT)
unnamed: U_EX5.3 (DOUT), U_RSHIFT1.2 (DIN)
unnamed: U_EX6.3 (DOUT), U_EX7.2 (DIN)
unnamed: U_EX7.3 (DOUT), U_EX8.2 (DIN)
unnamed: U_EX8.3 (DOUT), U_UP1.2 (DIN)
unnamed: U_F1.2 (DIN), U_F2.3 (DOUT)
unnamed: U_F2.2 (DIN), U_F3.3 (DOUT)
unnamed: U_F3.2 (DIN), U_F4.3 (DOUT)
unnamed: U_F4.2 (DIN), U_F5.3 (DOUT)
unnamed: U_F5.2 (DIN), U_F6.3 (DOUT)
unnamed: U_F6.2 (DIN), U_F7.3 (DOUT)
unnamed: U_F7.2 (DIN), U_F8.3 (DOUT)
unnamed: U_F8.2 (DIN), U_F9.3 (DOUT)
unnamed: U_F10.2 (DIN), U_F11.3 (DOUT)
unnamed: U_F9.2 (DIN), U_F10.3 (DOUT)
unnamed: U_F11.2 (DIN), U_F12.3 (DOUT)
unnamed: U_F12.2 (DIN), U_PRTSCR1.3 (DOUT)
unnamed: U_F13.3 (DOUT), U_G1.2 (DIN)
unnamed: U_FSLASH1.2 (DIN), U_RSHIFT1.3 (DOUT)
unnamed: U_FSLASH1.3 (DOUT), U_PERIOD1.2 (DIN)
unnamed: U_G1.3 (DOUT), U_H1.2 (DIN)
unnamed: U_H1.3 (DOUT), U_J1.2 (DIN)
unnamed: U_HOME1.2 (DIN), U_INSERT1.3 (DOUT)
unnamed: U_HOME1.3 (DOUT), U_PGUP1.2 (DIN)
unnamed: U_I1.2 (DIN), U_O1.3 (DOUT)
unnamed: U_I1.3 (DOUT), U_U1.2 (DIN)
unnamed: U_J1.3 (DOUT), U_K1.2 (DIN)
unnamed: U_K1.3 (DOUT), U_L1.2 (DIN)
unnamed: U_L1.3 (DOUT), U_SCOL1.2 (DIN)
unnamed: U_LALT1.2 (DIN), U_LSUPER1.3 (DOUT)
unnamed: U_LBRACK1.2 (DIN), U_RBRACK1.3 (DOUT)
unnamed: U_LBRACK1.3 (DOUT), U_P1.2 (DIN)
unnamed: U_LCTRL1.2 (DIN), U_LSHIFT1.3 (DOUT)
unnamed: U_LCTRL1.3 (DOUT), U_LSUPER1.2 (DIN)
unnamed: U_LEFT1.2 (DIN), U_RCTRL1.3 (DOUT)
unnamed: U_LSHIFT1.2 (DIN), U_Z1.3 (DOUT)
unnamed: U_M1.3 (DOUT), U_N1.2 (DIN)
unnamed: U_META1.2 (DIN), U_RSUPER1.3 (DOUT)
unnamed: U_META1.3 (DOUT), U_RCTRL1.2 (DIN)
unnamed: U_O1.2 (DIN), U_P1.3 (DOUT)
unnamed: U_PAUSE1.3 (DOUT), U_SLOC1.2 (DIN)
unnamed: U_PGDN1.2 (DIN), U_PGUP1.3 (DOUT)
unnamed: U_PRTSCR1.2 (DIN), U_SLOC1.3 (DOUT)
unnamed: U_Q1.2 (DIN), U_W1.3 (DOUT)
unnamed: U_Q1.3 (DOUT), U_TAB1.2 (DIN)
unnamed: U_QUOTE1.2 (DIN), U_SCOL1.3 (DOUT)
unnamed: U_R1.2 (DIN), U_T1.3 (DOUT)
unnamed: U_RALT1.3 (DOUT), U_RSUPER1.2 (DIN)
unnamed: U_T1.2 (DIN), U_Y1.3 (DOUT)
unnamed: U_U1.3 (DOUT), U_Y1.2 (DIN)
unnamed: U_X1.3 (DOUT), U_Z1.2 (DIN)
PWR: C1.1, C2.1, C3.1, C4.1, C5.1, C6.1, C7.1, C8.1, C9.1, C10.1, C11.1, C12.1, C13.1, C14.1, C15.1, C16.1, C17.1, C18.1, C19.1, C20.1, C21.1, C22.1, C23.1, C24.1, C25.1, C26.1, C27.1, C28.1, C29.1, C30.1, C31.1, C32.1, C33.1, C34.1, C35.1, C36.1, C37.1, C38.1, C39.1, C40.1, C41.1, C42.1, C43.1, C44.1, C45.1, C46.1, C47.1, C48.1, C49.1, C50.1, C51.1, C52.1, C53.1, C54.1, C55.1, C56.1, C57.1, C58.1, C59.1, C60.1, C61.1, C62.1, C63.1, C64.1, C65.1, C66.1, C67.1, C68.1, C69.1, C70.1, C71.1, C72.1, C73.1, C74.1, C75.1, C76.1, C77.1, C78.1, C79.1, C80.1, C81.1, C82.1, C83.1, C84.1, C85.1, C86.1, C87.1, C88.1, C89.1, C90.1, C91.1, C92.1, C93.1, C94.1, C95.1, J2.A4 (VBUS), J2.A9 (VBUS), J2.B4 (VBUS), J2.B9 (VBUS), U1.40 (VBUS), U2.5 (VCCB), U_0.4 (VCC), U_1.4 (VCC), U_2.4 (VCC), U_3.4 (VCC), U_4.4 (VCC), U_5.4 (VCC), U_6.4 (VCC), U_7.4 (VCC), U_8.4 (VCC), U_9.4 (VCC), U_A1.4 (VCC), U_ACCENT1.4 (VCC), U_B1.4 (VCC), U_BKSPC1.4 (VCC), U_BSLASH1.4 (VCC), U_C1.4 (VCC), U_CLOCK1.4 (VCC), U_COMMA1.4 (VCC), U_D1.4 (VCC), U_DASH1.4 (VCC)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
RGB_SIG: JP1.1 (A), U1.24 (GPIO18), U2.2 (A)
ROW 0: D_ESC1.1 (K), D_EX1.1 (K), D_F1.1 (K), D_F2.1 (K), D_F3.1 (K), D_F4.1 (K), D_F5.1 (K), D_F6.1 (K), D_F7.1 (K), D_F8.1 (K), D_F9.1 (K), D_F10.1 (K), D_F11.1 (K), D_F12.1 (K), D_PAUSE1.1 (K), D_PRTSCR1.1 (K), D_SLOC1.1 (K), U1.22 (GPIO17)
ROW 1: D_0.1 (K), D_1.1 (K), D_2.1 (K), D_3.1 (K), D_4.1 (K), D_5.1 (K), D_6.1 (K), D_7.1 (K), D_8.1 (K), D_9.1 (K), D_ACCENT1.1 (K), D_BKSPC1.1 (K), D_DASH1.1 (K), D_EQ1.1 (K), D_HOME1.1 (K), D_INSERT1.1 (K), D_PGUP1.1 (K), U1.25 (GPIO19)
ROW 2: D_BSLASH1.1 (K), D_DEL1.1 (K), D_E1.1 (K), D_END1.1 (K), D_I1.1 (K), D_LBRACK1.1 (K), D_O1.1 (K), D_P1.1 (K), D_PGDN1.1 (K), D_Q1.1 (K), D_R1.1 (K), D_RBRACK1.1 (K), D_T1.1 (K), D_TAB1.1 (K), D_U1.1 (K), D_W1.1 (K), D_Y1.1 (K), U1.26 (GPIO20)
ROW 3: D_A1.1 (K), D_CLOCK1.1 (K), D_D1.1 (K), D_ENT1.1 (K), D_EX4.1 (K), D_EX6.1 (K), D_EX7.1 (K), D_F13.1 (K), D_G1.1 (K), D_H1.1 (K), D_J1.1 (K), D_K1.1 (K), D_L1.1 (K), D_QUOTE1.1 (K), D_S1.1 (K), D_SCOL1.1 (K), U1.27 (GPIO21)
ROW 4: D_B1.1 (K), D_C1.1 (K), D_COMMA1.1 (K), D_EX5.1 (K), D_EX8.1 (K), D_FSLASH1.1 (K), D_LSHIFT1.1 (K), D_M1.1 (K), D_N1.1 (K), D_PERIOD1.1 (K), D_RSHIFT1.1 (K), D_UP1.1 (K), D_V1.1 (K), D_X1.1 (K), D_Z1.1 (K), U1.29 (GPIO22)
ROW 5: D_DOWN1.1 (K), D_EX2.1 (K), D_EX3.1 (K), D_LALT1.1 (K), D_LCRTL1.1 (K), D_LEFT1.1 (K), D_LSUPER1.1 (K), D_META1.1 (K), D_RALT1.1 (K), D_RCTRL1.1 (K), D_RIGHT1.1 (K), D_RSUPER1.1 (K), D_SPACE1.1 (K), U1.31 (GPIO26_ADC0)

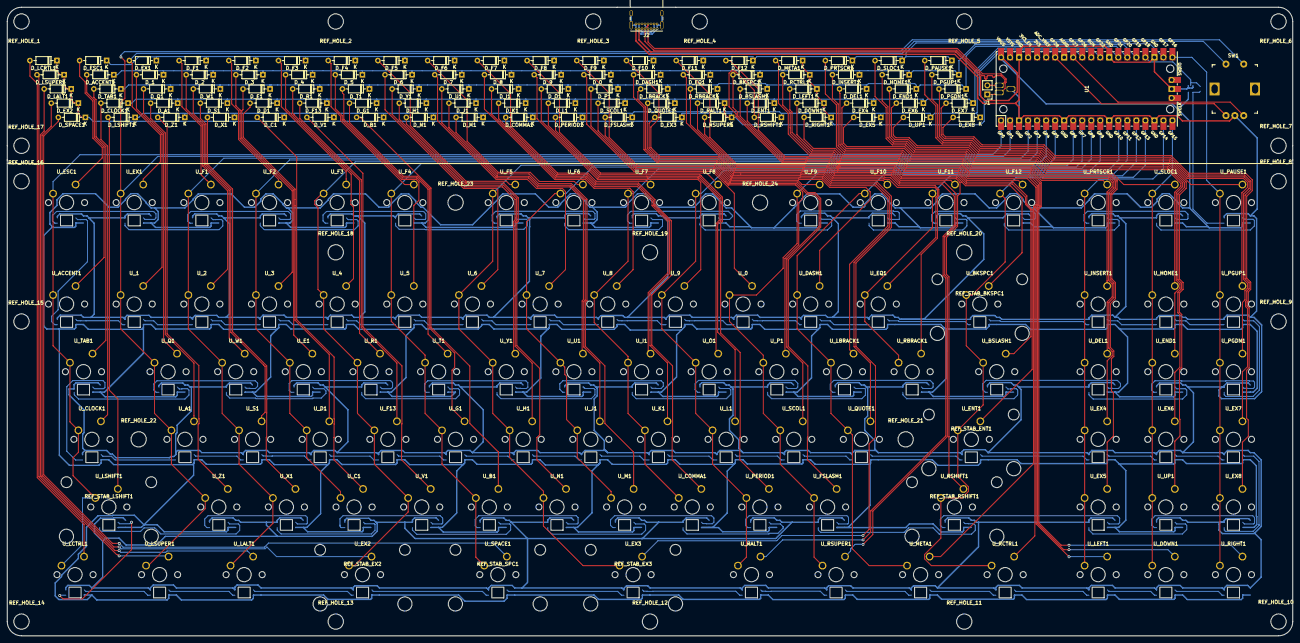
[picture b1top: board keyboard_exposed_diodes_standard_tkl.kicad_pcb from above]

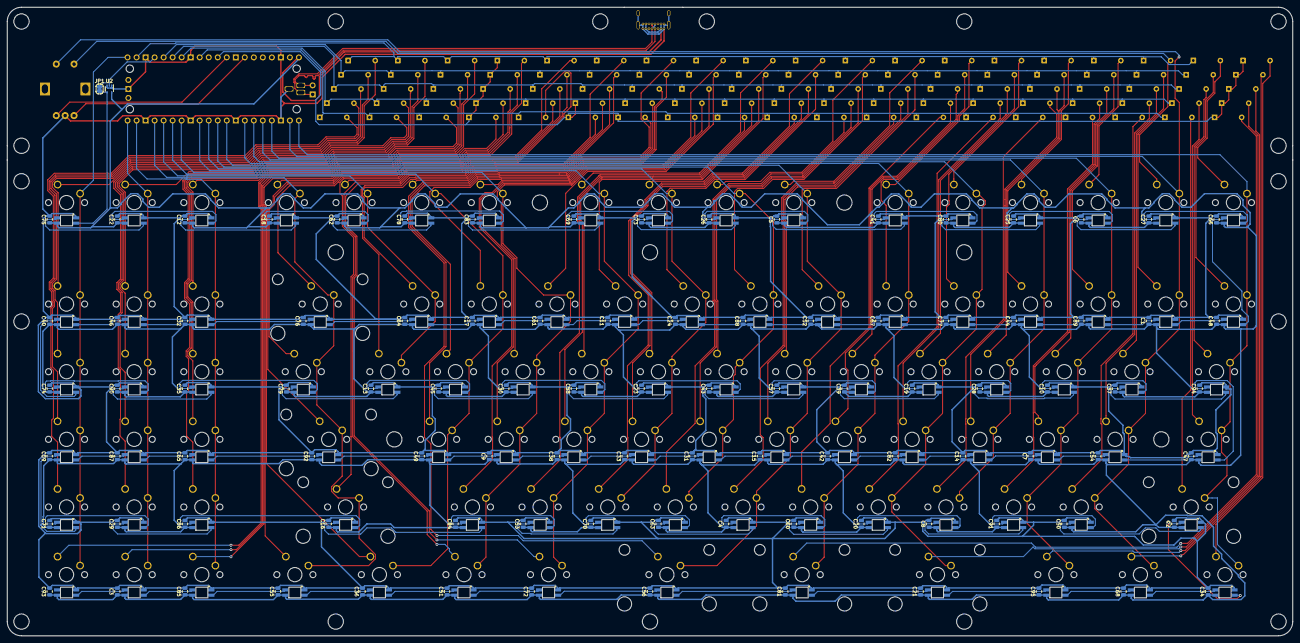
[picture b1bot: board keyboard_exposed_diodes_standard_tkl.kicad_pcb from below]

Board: 2 copper layers, 362.0 x 177.0 mm, 322 parts (97 on the bottom side), 220 nets.

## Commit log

2022-01-14 Add ignore gerber folder
2022-01-14 Add ignore gdsheet file
2022-01-14 First commit of project
2022-01-28 Move Libs to Project Level
2022-01-28 Adding Net Names
2022-01-28 Add board PCB image
2022-01-28 REduce PCB Spacing to match jlcpcb minimum. Redo USB C data traces
2022-01-28 Tune USB data line trace lengths
2022-02-13 Update pico footprint
2022-02-13 Add images
2022-02-13 Update images
2022-03-06 Move hole labels
2022-03-06 Remove gerber files from ignore
2022-03-06 Add gerber files for fab
2022-04-02 Remove Gerbers and backup
2022-04-02 Add footprint with expanded test point holes
2022-04-02 Modify earlier pcio footprint
2022-04-02 Remove step up led. Use gate instead
2022-04-03 Incude mount holes and stabilizer holes in schematic
2022-04-03 South facing gerber files
